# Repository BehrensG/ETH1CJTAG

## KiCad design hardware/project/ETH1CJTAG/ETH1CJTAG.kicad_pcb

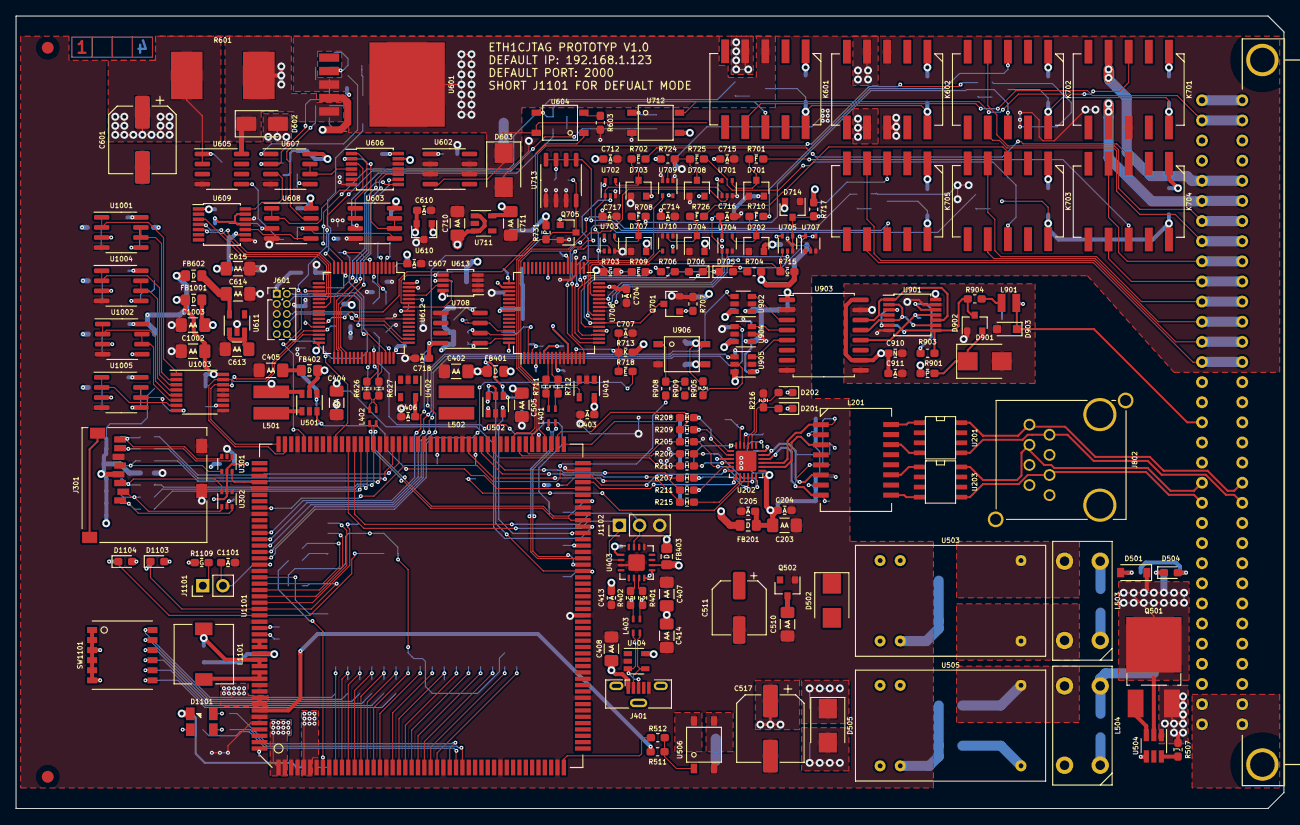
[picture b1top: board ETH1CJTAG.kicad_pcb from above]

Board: 4 copper layers, 160.0 x 100.0 mm, 458 parts (0 on the bottom side), 342 nets.

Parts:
C201, C202, C204, C205, C206, C207, C210, C212, C301, C302, C303, C403, C406, C409, C412, C413, C606, C607, C609, C612, C616, C619, C620, C621, C622, C626, C627, C628, C629, C630, C702, C704, C706, C707, C712, C713, C714, C715, C716, C717, C718, C719, C720, C721, C722, C723, C724, C901, C902, C903, C904, C905, C906, C907, C909, C911, C1001, C1005, C1006, C1007, C1008, C1009, C1101, C1104, C1105: 100n; C_0603_A_Pad1.05x0.95mm_HandSolder
C203, C304, C401, C402, C404, C405, C407, C408, C414, C502, C503, C505, C506, C509, C510, C613, C614, C615, C705, C710, C711, C725, C1002, C1003, C1103: 10u; C_1206_AA_Pad1.42x1.75mm_HandSolder
C208: 470p; C_0603_1608Metric_Pad1.05x0.95mm_HandSolder
C209, C605, C611, C908, C910, C1004: 1u; R_0603_N_Pad1.05x0.95mm_HandSolder
C211, C215: 1n/2kV; C_1206_3216Metric_Pad1.42x1.75mm_HandSolder
C213, C214, C624, C625, C708, C709: 8p; C_0603_S_Pad1.05x0.95mm_HandSolder
C410, C411, C912: 47p; C_0603_1608Metric_Pad1.05x0.95mm_HandSolder
C501, C504: 27p; C_0603_1608Metric_Pad1.05x0.95mm_HandSolder
C507, C512, C513, C518: 470p/2kV; C_1206_3216Metric_Pad1.42x1.75mm_HandSolder
C508, C514: 2u2/100V; C_1206_3216Metric_Pad1.42x1.75mm_HandSolder
C511: 100u; CP_Elec_6.3x5.9
C515, C516, C602, C603, C604: 10u/50V; C_1206_3216Metric_Pad1.42x1.75mm_HandSolder
C517, C601: 220u/50V; CP_Elec_8x6.9
C608, C623, C701, C703, C1102: 4u7; C_0805_M_Pad1.15x1.40mm_HandSolder
C610: 10u; C_0603_A_Pad1.05x0.95mm_HandSolder
C617, C618: 2u2; C_0603_1608Metric_Pad1.05x0.95mm_HandSolder
C631, C632: 2p2; C_0603_1608Metric_Pad1.05x0.95mm_HandSolder
D201: YELLLOW; LED_0603_1608Metric_Pad1.05x0.95mm_HandSolder
D202, D1103, D1104: GREEN; LED_0603_1608Metric_Pad1.05x0.95mm_HandSolder
D501: MMSZ5249B-E3-18; D_SOD-123
D502: P6SMB6.8CA; D_SMB
D503: SM6T30AY; DO_214AA_REV
D504: RED; LED_0603_1608Metric_Pad1.05x0.95mm_HandSolder
D505, D603: P6SMB30CA; D_SMB
D601, D604, D709, D710, D711, D712, D713: 1N4148W; D_SOD-123
D602: SK33A; D_SMA
D701, D702, D703, D704, D707, D708, D714: BAT54S; SOT-23
D705, D706: LED; LED_0603_1608Metric_Pad1.05x0.95mm_HandSolder
D901: SMBJ5.0A; D_SMB
D902: BAV99; SOT-23
D903: SD36C-01FTG; D_SOD-323_HandSoldering
D1101: 150121M153000
D1102: PMEG4005AEA; D_SOD-323
F501: MF-LSMF185/33X; Fuse_SMD2920
FB201, FB401, FB402, FB403, FB501, FB502, FB503, FB504, FB601, FB602, FB701, FB1001: 742792031; R_0805_D_Pad1.15x1.40mm_HandSolder
FID101, FID102, FID103, FID104: Fiducial; Fiducial_1.5mm_Mask3mm
J301: 693071010811
J401: 105133-0001; USB_Micro-B_Molex-105133-0001
J601: Conn_02x05; PinHeader_2x05_P1.27mm_Vertical
J801: C64AC; Socket_DIN41612-CaseC1-AC-Male-64Pin-2rows
J802: 615008145221
J1101: Conn_01x02; PinHeader_1x02_P2.54mm_Vertical
J1102: Conn_01x03_Male; PinHeader_1x03_P2.54mm_Vertical
J1103: Conn_02x10_Counter_Clockwise; PinHeader_2x10_P1.27mm_Vertical_SMD
K601, K602, K701, K702, K703, K704, K705: TQ2SA-5V; SA
L201: 749010012A
L401, L402, L403: 744233121
L501, L502: 4u7; 744031004
L503, L504: 7448014501
L901: CW252016-R33G; CW252016
L1101: 851-CDRH74NP-180MC; CDRH74
Q501: IRFR5410; TO-252-2_Rectifier
Q502: TSM2323; SOT-23
Q601, Q602: MMBT3904; SOT-23
Q603, Q702, Q703, Q704, Q705: BC847; SOT-23
Q701: 2SD1048; SOT-23
R201, R202, R203, R204, R1147: 49R9; R_0603_1608Metric_Pad1.05x0.95mm_HandSolder
R205, R206, R207, R208, R209, R210, R211, R215, R626, R627, R711, R712, R1110, R1111, R1112, R1113, R1114, R1115: 22; R_0603_H_Pad1.05x0.95mm_HandSolder
R212: 12k1; R_0603_1608Metric_Pad1.05x0.95mm_HandSolder
R213, R214: 75/1%; R_0603_1608Metric_Pad1.05x0.95mm_HandSolder
R216, R220, R221, R222, R301, R302, R303, R304, R305, R306, R503, R506, R612, R618, R619, R623, R703, R715, R716, R720, R721, R722, R905, R1003, R1004, R1007, R1008, R1011, R1012, R1015, R1016, R1109, R1117, R1118, R1119, R1120, R1121, R1122, R1123, R1124, R1125, R1128, R1129, R1130, R1131, R1132, R1133, R1134, R1135, R1144, R1146, R1148: 10k; R_0603_G_Pad1.05x0.95mm_HandSolder
R217, R218, R1142, R1143: 470; R_0603_1608Metric_Pad1.05x0.95mm_HandSolder
R219: 1M/1kV; R_1206_3216Metric_Pad1.42x1.75mm_HandSolder
R401, R402: 22; R_0603_G_Pad1.05x0.95mm_HandSolder
R501, R504: 180k; R_0603_1608Metric_Pad1.05x0.95mm_HandSolder
R502, R505: 20k; R_0603_1608Metric_Pad1.05x0.95mm_HandSolder
R507, R622, R630, R631, R1001: 100k; R_0603_J_Pad1.05x0.95mm_HandSolder
R508: 6k8/0.5W; R_0805_2012Metric_Pad1.15x1.40mm_HandSolder
R509: 370; R_0603_1608Metric_Pad1.05x0.95mm_HandSolder
R510, R907: 0/0.75W; R_1206_3216Metric_Pad1.42x1.75mm_HandSolder
R511, R512, R603, R727, R908, R909: 420; R_0603_1608Metric_Pad1.05x0.95mm_HandSolder
R601: WSR21R000FEB; WSR
R602, R610: 100/0.1%; R_0603_1608Metric_Pad1.05x0.95mm_HandSolder
R604, R605: 50k/0.1%; R_0603_1608Metric_Pad1.05x0.95mm_HandSolder
R606, R607: 22k/0.1%; R_0603_1608Metric_Pad1.05x0.95mm_HandSolder
R608, R1106, R1107: 330; R_0603_1608Metric_Pad1.05x0.95mm_HandSolder
R609: 1k/0.1%; R_0603_1608Metric_Pad1.05x0.95mm_HandSolder
R611, R709, R718, R730, R1101, R1102, R1103, R1104, R1145: 0; R_0603_E_Pad1.05x0.95mm_HandSolder
R613, R615, R616, R617: 10k/0.1%; R_0603_1608Metric_Pad1.05x0.95mm_HandSolder
R614: 3k2; R_0603_L_Pad1.05x0.95mm_HandSolder
R620, R628, R629, R632, R633, R713: 4k7; R_0603_K_Pad1.05x0.95mm_HandSolder
R621, R728, R729, R731, R732, R733, R901: 1k; R_0603_P_Pad1.05x0.95mm_HandSolder
R624, R625: 560; R_0603_1608Metric_Pad1.05x0.95mm_HandSolder
R701, R702, R708, R710, R719, R725, R726: 82; R_0603_F_Pad1.05x0.95mm_HandSolder
R704, R706: 270; R_0603_1608Metric_Pad1.05x0.95mm_HandSolder
R705: 15k; R_0603_1608Metric_Pad1.05x0.95mm_HandSolder
R707, R717, R724: 22k; R_0603_1608Metric_Pad1.05x0.95mm_HandSolder
R714: 12k; R_0603_1608Metric_Pad1.05x0.95mm_HandSolder
R723: 2k2; R_0603_1608Metric_Pad1.05x0.95mm_HandSolder
R902: 14k7; R_0603_1608Metric_Pad1.05x0.95mm_HandSolder
R903: 100; R_0603_1608Metric_Pad1.05x0.95mm_HandSolder
R904: 47; R_0603_1608Metric_Pad1.05x0.95mm_HandSolder
R906: 51R1; R_0603_1608Metric_Pad1.05x0.95mm_HandSolder
R1002, R1006, R1014: 5k; R_0603_1608Metric_Pad1.05x0.95mm_HandSolder
R1005, R1009, R1010, R1013: 13k; R_0603_1608Metric_Pad1.05x0.95mm_HandSolder
R1105: 523; R_0603_1608Metric_Pad1.05x0.95mm_HandSolder
R1108: 1k5; R_0603_1608Metric_Pad1.05x0.95mm_HandSolder
R1116: 75k; R_0603_1608Metric_Pad1.05x0.95mm_HandSolder
R1126: 130k; R_0603_1608Metric_Pad1.05x0.95mm_HandSolder
R1127: 680k; R_0603_1608Metric_Pad1.05x0.95mm_HandSolder
R1136, R1137, R1138, R1139, R1140, R1141: 47k; R_0603_I_Pad1.05x0.95mm_HandSolder
SW1101: TDA06H0B1
U201, U203: LC03-3.3; SO8E
U202: LAN8720A; QFN-24-1EP_4x4mm_P0.5mm_EP2.6x2.6mm
U204, U301, U302: 82400274; SOT-363_SC-70-6
U401, U402, U404: 824011; SOT-23-5
U403: FT230XQ; QFN-16-1EP_4x4mm_P0.65mm_EP2.1x2.1mm
U501, U502: TPS61073; SOT-23-6
U503: TEL 10-2411WI; TEL10
U504: MAX5902; SOT-23-6_Handsoldering
U505: TEL 10-2415WI; TEL10
U506, U604, U712, U906: AQY212GS
U601: LT3080EQ; DD-PAK
U602: LM334M; SOIC-8_3.9x4.9mm_P1.27mm
U603, U607, U608, U1001, U1002, U1004, U1005: TLC272; SOIC-8_3.9x4.9mm_P1.27mm
U605: MAX4080FASA+; SOIC-8_3.9x4.9mm_P1.27mm
U606: MCP3204; TSSOP-14_4.4x5mm_P0.65mm
U609: MCP4922-ESL; TSSOP-14_4.4x5mm_P0.65mm
U610: REF3025; SOT-23
U611, U711: TLV75533PDBV; SOT-23-5
U612: STM32F405RGT6; LQFP-64_10x10mm_P0.5mm
U613: 24LC256; MSOP-8_3x3mm_P0.65mm
U701, U702, U703, U704, U705, U707, U709, U710: NC7SZ125; SOT-353_SC-70-5
U706: FT2232H; LQFP-64_10x10mm_P0.5mm
U708: 93LC56; SOIC-8_3.9x4.9mm_P1.27mm
U713: IRF7455; SO-8_3.9x4.9mm_P1.27mm
U901: 74AC125; TSSOP-14_4.4x5mm_P0.65mm
U902, U904, U905: SN74LVC1T45DBV; SOT-23-6
U903: ADuM5402; SOIC-16W_7.5x10.3mm_P1.27mm
U1003: ADS7828; TSSOP-16_4.4x5mm_P0.65mm
U1101: chiliSOM; GCS2
Y201: ECS-250-8-36CKM-TR; ECX-2236
Y601, Y701: ECS-120-8-36-CKM-TR; ECX-2236
Y602: 32.768kHz; ABS06W

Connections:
3.3V_DBG: C412.1, U403.1, U403.8, U403.9
5V_ISO_TRIG: C909.1, C910.1, C911.1, R901.1, U901.14, U903.10, U903.16
5V_TRIG: C904.1, C905.1, C906.1, C907.1, C908.1, R905.2, R907.2, U902.1, U903.1, U904.1, U905.1, U906.4
5V_USB: C407.1, C413.1, C414.1, FB403.2, U403.10, U1101.5, U1101.6
+1.8V_JTAG: C705.1, C706.1, U706.12, U706.37, U706.49, U706.64
+2V5: C610.1, R611.2, U606.13, U609.11, U609.13, U610.2
+3.3VA: R511.2, R909.2, U1101.178
+3.3V_D: C201.1, C202.1, C301.1, C302.1, C303.1, C304.1, C901.1, C902.1, C903.1, C1003.1, C1104.1, D1101.1, FB201.2, FB1001.1, J301.4, J1103.3, R220.1, R221.1, R222.1, R301.1, R302.1, R303.1, R304.1, R305.1, R306.1, R1014.1, R1108.1, R1109.1, R1117.1, R1118.1, R1119.1, R1142.1, R1143.1, R1144.1, R1146.1, R1148.1, SW1101.1, SW1101.2, SW1101.3, SW1101.4, SW1101.5, SW1101.6, U202.9, U301.5, U302.5, U902.6, U904.6, U905.6, U1101.176, U1101.177
+3.3V_JTAG: C701.1, C702.1, C703.1, C704.1, C712.1, C713.1, C714.1, C715.1, C716.1, C717.1, C718.1, C719.1, C720.1, C721.1, C722.1, C723.1, C724.1, C725.1, D701.2, D702.2, D703.2, D704.2, D707.2, D708.2, D714.2, FB701.1, R703.1, R704.1, R705.2, R706.1, R713.1, R715.2, R716.2, R717.1, R720.1, R721.1, R722.1, R724.1, R731.2, R1002.1, U701.5, U702.5, U703.5, U704.5, U705.5, U706.4, U706.9, U706.20, U706.31, U706.42, U706.50, U706.56, U707.5, U708.8, U709.5, U710.5, U712.3
+3.3V_PSU: C611.1, C612.1, C615.1, C619.1, C620.1, C621.1, C622.1, C623.1, C626.1, C627.1, C628.1, FB601.1, FB602.1, J601.1, R614.1, R620.1, R622.1, R628.1, R629.1, R632.1, R633.1, R1006.1, U603.8, U606.14, U607.8, U609.1, U609.9, U610.1, U612.19, U612.32, U612.48, U612.64, U613.8
+3.3V_TEST: C1002.1, C1004.1, C1005.1, C1006.1, C1007.1, C1008.1, C1009.1, FB1001.2, U1001.8, U1002.8, U1003.16, U1004.8, U1005.8
+5VD: C511.1, D601.1, D604.1, D709.1, D710.1, D711.1, D712.1, D713.1, K601.1, K602.1, K701.1, K702.1, K703.1, K704.1, K705.1, Q502.2, R907.1, R1005.1, U906.3, U1101.1, U1101.2
+24V: F501.1, J801.A31, J801.A32, J801.C31, J801.C32
+24V_PSU: C601.1, C629.1, C630.1, R510.1, R601.2, R1001.1, U506.4, U601.4, U605.1, U605.2, U608.8
/Connector/+VOUT: J801.A1, J801.C1, K601.4
/Connector/-VOUT: J801.A3, J801.C3, K602.4, K602.7
/Connector/EXT_TRIG: C912.1, D903.1, J801.A17, L901.1
/Connector/JTAG_GND: J801.A6, J801.C6, K701.7
/Connector/JTAG_VCC: J801.A5, J801.C5, K701.4
/Connector/RCTK: J801.A11, J801.C11, K703.4
/Connector/RX+: J801.A20, J802.3, U203.8
/Connector/RX-: J801.A21, J802.6, U203.5
/Connector/SENSE: J801.A2, J801.C2, K601.7
/Connector/SRST: J801.A13, J801.C13, K705.4
/Connector/TCK: J801.A10, J801.C10, K704.7
/Connector/TDI: J801.A8, J801.C8, K702.7
/Connector/TDO: J801.A12, J801.C12, K703.7
/Connector/TMS: J801.A9, J801.C9, K704.4
/Connector/TRST: J801.A7, J801.C7, K702.4
/Connector/TX+: J801.C20, J802.1, U201.8
/Connector/TX-: J801.C21, J802.2, U201.5
/Connector/nRESET: J801.A14, J801.C14, K705.7
/Ethernet/ETH_CRS_DV: R211.2, U1101.106
/Ethernet/ETH_MDC: U202.13, U1101.89
/Ethernet/ETH_MDIO: R1108.2, U202.12, U1101.90
/Ethernet/ETH_MODE0: R208.1, R220.2, U202.8
/Ethernet/ETH_MODE1: R209.1, R221.2, U202.7
/Ethernet/ETH_MODE2: R211.1, R222.2, U202.11
/Ethernet/ETH_RD_N: L201.8, R204.2, U202.22, U204.1
/Ethernet/ETH_RD_P: L201.6, R203.2, U202.23, U204.3
/Ethernet/ETH_REFCLK: R215.2, U1101.108
/Ethernet/ETH_RESETn: C212.1, R1104.1, U202.15
/Ethernet/ETH_RXD0: R208.2, U1101.93
/Ethernet/ETH_RXD1: R209.2, U1101.94
/Ethernet/ETH_RXERR: R210.2, U1101.104
/Ethernet/ETH_TD_N: L201.3, R202.2, U202.20, U204.4
/Ethernet/ETH_TD_P: L201.1, R201.2, U202.21, U204.6
/Ethernet/ETH_TXD0: R205.2, U1101.99
/Ethernet/ETH_TXD1: R206.2, U1101.100
/Ethernet/ETH_TXEN: R207.2, U1101.105
/JTAG/3V3_JTAG_CTR: R727.2, U1101.134
/JTAG/FT_EECLK: R721.2, U706.62, U708.2
/JTAG/FT_EECS: R720.2, U706.63, U708.1
/JTAG/FT_EEDATA: R723.1, U706.61, U708.3
/JTAG/FT_JTAG_OE_N: R703.2, R709.1, U701.1, U702.1, U703.1
/JTAG/FT_RCTK: U706.24, U710.4
/JTAG/FT_SRST_N_IN: D706.1, U706.23, U707.4
/JTAG/FT_SRST_N_OE_N: R715.1, U705.1, U706.29
/JTAG/FT_SRST_N_OUT: U705.2, U706.27
/JTAG/FT_TCK_OUT: U701.2, U706.16
/JTAG/FT_TDI_OUT: U703.2, U706.17
/JTAG/FT_TDO_IN: U706.18, U709.4
/JTAG/FT_TMS_OUT: U702.2, U706.19
/JTAG/FT_TRST_N_OE_N: R716.1, U704.1, U706.28
/JTAG/FT_TRST_N_OUT: U704.2, U706.26
/JTAG/FT_VREF_N_IN: D705.1, Q701.3, U706.22
/JTAG/FT_~RESET: R718.2, U1101.154
/JTAG/F_USB1_D_N: L401.3, R712.2, U401.4
/JTAG/F_USB1_D_P: L401.2, R711.2, U401.3
/JTAG/JTAG_REL1: D711.2, D712.2, K703.10, K704.10, Q704.3
/JTAG/JTAG_REL2: D709.2, D710.2, K701.10, K702.10, Q702.3
/JTAG/JTAG_REL3: D713.2, K705.10, Q703.3
/JTAG/JTAG_REL_CTR1: R732.2, U1101.96
/JTAG/JTAG_REL_CTR2: R728.2, U1101.101
/JTAG/JTAG_REL_CTR3: R729.2, U1101.98
/JTAG/RCTK1: K703.3, R726.1
/JTAG/RCTK1_A: D704.3, R726.2, U710.2
/JTAG/SRST1: K705.3, R719.1
/JTAG/SRST1_A: D714.3, R717.2, R719.2, U705.4, U707.2
/JTAG/TCK1: K704.8, R701.1
/JTAG/TCK1_A: D701.3, R701.2, U701.4
/JTAG/TDI1: K702.8, R708.1
/JTAG/TDI1_A: D707.3, R708.2, U703.4
/JTAG/TDO1: K703.8, R725.1
/JTAG/TDO1_A: D708.3, R724.2, R725.2, U709.2
/JTAG/TMS1: K704.3, R702.1
/JTAG/TMS1_A: D703.3, R702.2, U702.4
/JTAG/TRST1: K702.3, R710.1
/JTAG/TRST1_A: D702.3, R710.2, U704.4
/JTAG/nRESET1: K705.8, R730.1, U713.5, U713.6, U713.7, U713.8
/JTAG/nRESET_OUT: R733.2, U1101.150
/PSU/CLIM: Q602.3, U612.16
/PSU/F_USB0_D_N: L402.2, R626.1, U402.4
/PSU/F_USB0_D_P: L402.3, R627.1, U402.3
/PSU/I2C_SCL: R632.2, U612.29, U1003.14, U1101.138
/PSU/I2C_SDA: R633.2, U612.30, U1003.15, U1101.137
/PSU/ISET: U608.5, U609.10
/PSU/NC\TDI: J601.8, U612.50
/PSU/PSU_ADC_CLK: U606.11, U612.34
/PSU/PSU_ADC_IOUT: C605.1, R608.1, U603.5, U608.6
/PSU/PSU_ADC_SDI: U606.9, U612.36
/PSU/PSU_ADC_SDO: U606.10, U612.35
/PSU/PSU_ADC_VOUT: C606.1, R604.1, R606.2, R607.2, U603.3
/PSU/PSU_ADC_~CS: U606.8, U612.33
/PSU/PSU_DAC_SCK: U609.4, U612.21
/PSU/PSU_DAC_SDI: U609.5, U612.23
/PSU/PSU_DAC_~CS: U609.3, U612.20
/PSU/PSU_I2C_SCL: R628.2, U612.58, U613.6
/PSU/PSU_I2C_SDA: R629.2, U612.59, U613.5
/PSU/PSU_NRST: C616.1, J601.10, R620.2, U612.7, U1101.129
/PSU/PSU_RELAY: D601.2, D604.2, K601.10, K602.10, Q603.3
/PSU/PSU_SENSE: U604.1, U612.27
/PSU/PSU_WP: U612.61, U613.7
/PSU/SWDCLK\TCK: J601.4, U612.49
/PSU/SWDIO\TMS: J601.2, U612.46
/PSU/SWO\TDO: J601.6, U612.55
/PSU/USB0_ID: R625.1, R1101.2, R1102.1
/PSU/VSET: U607.3, U609.14
/Power/ENA_24V_PSU: R512.2, U1101.46
/Power/USB0_DRVVBUS: R503.1, U501.3, U1101.88
/Power/USB1_DRVVBUS: R506.1, U502.3, U1101.81
/SOM/BOOT0: R1125.2, R1141.1, U1101.10
/SOM/BOOT1: R1124.2, R1140.1, U1101.11
/SOM/BOOT2: R1123.2, R1139.1, U1101.12
/SOM/BOOT3: R1122.2, R1138.1, U1101.13
/SOM/BOOT4: R1121.2, R1137.1, U1101.14
/SOM/BOOT5: R1120.2, R1136.1, U1101.15
/SOM/BOOT6: R1119.2, U1101.16
/SOM/BOOT7: R1135.1, U1101.17
/SOM/BOOT8: R1134.1, U1101.19
/SOM/BOOT9: R1118.2, R1133.1, U1101.20
/SOM/BOOT10: R1132.1, U1101.21
/SOM/BOOT11: R1131.1, U1101.22
/SOM/BOOT12: R1130.1, U1101.23
/SOM/BOOT13: R1129.1, U1101.24
/SOM/BOOT14: R1117.2, U1101.25
/SOM/BOOT15: R1128.1, U1101.26
/SOM/DBG_RXD: J1102.2, U403.15, U1101.126
/SOM/DBG_TXD: J1102.1, U403.2, U1101.127
/SOM/ENA_5V_TRIG: R908.2, U1101.146
/SOM/LED_BLUE: R1107.2, U1101.28
/SOM/LED_GREEN: R1106.2, U1101.30
/SOM/LED_RED: R1105.2, U1101.29
/SOM/SD_CD: J301.9, R306.2, U301.6, U1101.142
/SOM/SD_CLK: J301.5, R1110.2, U301.4
/SOM/SD_CMD: J301.3, R303.2, R1111.2, U302.6
/SOM/SD_DAT0: J301.7, R304.2, R1112.2, U301.1
/SOM/SD_DAT1: J301.8, R305.2, R1113.2, U301.3
/SOM/SD_DAT2: J301.1, R301.2, R1114.2, U302.3
/SOM/SD_DAT3: J301.2, R302.2, R1115.2, U302.1
/SOM/TRIG_EN: U902.4, U1101.153
/SOM/TRIG_IN: U905.4, U1101.151
/SOM/TRIG_OUT: U904.4, U1101.152
/SOM/USB0_D_N: L402.1, U1101.83
/SOM/USB0_D_P: L402.4, U1101.84
/SOM/USB1_D_N: L401.4, U1101.76
/SOM/USB1_D_P: L401.1, U1101.77
/SOM/chili_EMU0: D1104.1, J1103.7, R1144.2, U1101.163
/SOM/chili_EMU1: D1103.1, J1103.14, R1146.2, U1101.162
/SOM/chili_RESETn: C1105.1, R1147.2, R1148.2, U1101.8
/SOM/chili_TCK: J1103.6, R1145.2, U1101.158
/SOM/chili_TDI: J1103.2, U1101.160
/SOM/chili_TDO: J1103.4, U1101.159
/SOM/chili_TMS: J1103.1, U1101.161
/SOM/chili_~TRST: J1103.20, U1101.157
/Test/CH0: U1001.1, U1001.2, U1003.1
/Test/CH1: U1001.6, U1001.7, U1003.2
/Test/CH2: U1003.3, U1004.1, U1004.2
/Test/CH3: U1003.4, U1004.6, U1004.7
/Test/CH4: U1002.1, U1002.2, U1003.5
/Test/CH5: U1002.6, U1002.7, U1003.6
/Test/CH6: U1003.7, U1005.1, U1005.2
/Test/CH7: U1003.8, U1005.6, U1005.7
/Trigger/EXT_TRIG_SIGN: R902.1, U901.11, U903.12
/Trigger/TRIG_OUT_EN: U901.1, U901.4, U901.10, U903.14
/Trigger/TRIG_OUT_SIGN: U901.2, U901.5, U901.9, U903.13
/USB/DBG_USB_D_N: C410.1, L403.1, R401.1
/USB/DBG_USB_D_P: C411.1, L403.4, R402.1
/USB/F_DBG_USB_D_N: J401.2, L403.2, U404.4
/USB/F_DBG_USB_D_P: J401.3, L403.3, U404.3
DBG_USB_VCC: C408.1, C409.1, FB403.1, J401.1, U404.5
Earth: C211.2, C215.1, J801.A19, J801.A23, J801.C19, J801.C23, J802.SH, R219.1
GND: C909.2, C910.2, C911.2, D901.2, D902.1, D903.2, J801.C17, R906.2, U901.7, U901.13, U903.9, U903.15
GNDA: C201.2, C202.2, C203.2, C204.2, C205.2, C206.2, C207.2, C208.2, C209.2, C210.2, C212.2, C213.2, C214.2, C215.2, C301.2, C302.2, C303.2, C304.2, C401.2, C402.2, C403.2, C404.2, C405.2, C406.2, C407.2, C408.2, C409.2, C410.2, C411.2, C412.2, C413.2, C414.2, C502.2, C503.2, C505.2, C506.2, C510.2, C511.2, C516.2, C517.2, C601.2, C602.2, C603.2, C604.2, C605.2, C606.2, C607.2, C608.2, C609.2, C610.2, C611.2, C612.2, C613.2, C614.2, C615.2, C616.2, C617.2, C618.2, C619.2, C620.2, C621.2, C622.2, C623.2, C624.2, C625.2, C626.2, C627.2, C628.2, C629.2, C630.2, C631.2, C632.2, C701.2, C702.2, C703.2, C704.2, C705.2, C706.2, C707.2, C708.2, C709.2, C710.2, C711.2, C712.2, C713.2, C714.2, C715.2, C716.2, C717.2, C718.2, C719.2, C720.2, C721.2, C722.2, C723.2, C724.2, C725.2, C901.2, C902.2, C903.2, C904.2, C905.2, C906.2, C907.2, C908.2, C1001.2, C1002.2, C1003.2, C1004.2, C1005.2, C1006.2, C1007.2, C1008.2, C1009.2, C1101.2, C1102.1, C1103.2, C1104.2, C1105.2, D603.2, D701.1, D702.1, D703.1, D704.1, D707.1, D708.1, D714.1, FB502.2, FB504.2, J301.6, J301.10, J401.5, J601.3, J601.5, J1102.3, J1103.11, J1103.13, J1103.15, J1103.16, J1103.17, J1103.19, K602.3, K602.8, K701.8, Q502.1, Q601.2, Q602.2, Q603.2, Q701.2, Q702.2, Q703.2, Q704.2, Q705.2, R212.1, R216.2, R217.2, R218.2, R219.2, R502.2, R503.2, R505.2, R506.2, R602.2, R603.1, R606.1, R607.1, R613.2, R615.2, R618.2, R623.2, R630.1, R631.1, R707.1, R714.2, R1003.2, R1004.2, R1007.2, R1008.2, R1011.2, R1012.2, R1015.2, R1016.2, R1101.1, R1103.1, R1116.2, R1126.1, R1127.1, R1128.2, R1129.2, R1130.2, R1131.2, R1132.2, R1133.2, R1134.2, R1135.2, R1136.2, R1137.2, R1138.2, R1139.2, R1140.2, R1141.2, U202.25, U204.2, U301.2, U302.2, U401.2, U402.2, U403.3, U403.13, U403.17, U404.2, U501.2, U502.2, U506.2, U602.2, U602.3, U602.6, U602.7, U603.4, U605.4, U606.7, U606.12, U607.4, U608.4, U609.8, U609.12, U610.3, U611.2, U612.12, U612.18, U612.63, U613.1, U613.2, U613.3, U613.4, U701.3, U702.3, U703.3, U704.3, U705.3, U706.1, U706.5, U706.10, U706.11, U706.13, U706.15, U706.25, U706.35, U706.47, U706.51, U707.1, U707.3, U708.5, U709.1, U709.3, U710.1, U710.3, U711.2, U712.2, U713.1, U713.2, U713.3, U902.2, U902.5, U903.2, U903.8, U904.2, U904.5, U905.2, U906.2, U1001.4, U1002.4, U1003.9, U1003.11, U1003.12, U1003.13, U1004.4, U1005.4, U1101.3, U1101.4, U1101.9, U1101.18, U1101.27, U1101.36, U1101.45, U1101.55, U1101.68, U1101.78, U1101.85, U1101.91, U1101.97, U1101.109, U1101.118, U1101.121, U1101.130, U1101.135, U1101.143, U1101.147, U1101.156, U1101.164, U1101.174, U1101.175, U1101.179, U1101.180, Y201.2, Y201.4, Y601.2, Y601.4, Y701.2, Y701.4
GNDPWR: C508.2, C514.2, D503.2, D504.1, J801.A27, J801.A28, J801.C27, J801.C28, L503.2, L504.2, U504.4
unnamed: C203.1, C204.1, C205.1, C206.1, C207.1, C210.1, FB201.1, L201.2, L201.7, R201.1, R202.1, R203.1, R204.1, U202.1, U202.19
unnamed: C208.1, C209.1, U202.6
unnamed: C211.1, R213.2, R214.2
unnamed: C213.1, U202.5, Y201.1
unnamed: C214.1, U202.4, Y201.3
unnamed: C501.2, R501.2, R502.1, U501.4
unnamed: C504.2, R504.2, R505.1, U502.4
unnamed: C507.1, L503.4, U503.16
unnamed: C507.2, C509.2, C512.2, D502.2, FB502.1, U503.10
unnamed: C508.1, C514.1, D501.1, L503.1, L504.1, Q501.2, R508.1, U504.2
unnamed: C509.1, D502.1, FB501.1, U503.9
unnamed: C510.1, FB501.2, Q502.3
unnamed: C512.1, L503.3, U503.1
unnamed: C513.1, L504.4, U505.16
unnamed: C513.2, C515.2, C518.2, D505.2, FB504.1, U505.10
unnamed: C515.1, D505.1, FB503.1, U505.9
unnamed: C516.1, C517.1, FB503.2, R510.2, U506.3
unnamed: C518.1, L504.3, U505.1
unnamed: C602.1, D602.2, D603.1, K601.3, U601.3, U601.6, U602.4, U604.4
unnamed: C603.1, D602.1, R601.1, U601.5, U605.8
unnamed: C604.1, R610.1, R617.1, U601.2
unnamed: C607.1, U612.1
unnamed: C608.1, C609.1, FB601.2, U612.13
unnamed: C614.1, FB602.2, U611.5
unnamed: C617.1, U612.31
unnamed: C618.1, U612.47
unnamed: C624.1, U612.5, Y601.3
unnamed: C625.1, U612.6, Y601.1
unnamed: C631.1, U612.4, Y602.1
unnamed: C632.1, U612.3, Y602.2
unnamed: C707.1, R713.2, R718.1, U706.14
unnamed: C708.1, U706.2, Y701.1
unnamed: C709.1, U706.3, Y701.3
unnamed: C711.1, FB701.2, U711.5
unnamed: C912.2, R906.1
unnamed: C1001.1, U1003.10
unnamed: C1101.1, J1101.2, U1101.155
unnamed: C1102.2, D1102.1, U1101.169
unnamed: C1103.1, U1101.113
unnamed: D201.1, R217.1
unnamed: D201.2, R216.1, U202.2
unnamed: D202.1, R218.1
unnamed: D202.2, U202.3
unnamed: D501.2, R509.1
unnamed: D503.1, F501.2, Q501.3, R507.1, U504.1
unnamed: D504.2, R508.2, R509.2
unnamed: D705.2, R704.2
unnamed: D706.2, R706.2
unnamed: D901.1, D902.2, R901.2
unnamed: D902.3, R903.2, R904.1, U901.3, U901.6, U901.8
unnamed: D1101.2, R1105.1
unnamed: D1101.3, R1106.1
unnamed: D1101.4, R1107.1
unnamed: D1102.2, L1101.2, U1101.170, U1101.171
unnamed: D1103.2, R1142.2
unnamed: D1104.2, R1143.2
unnamed: J1101.1, R1109.2
unnamed: J1103.5, R1145.1
unnamed: J1103.8, R1147.1
unnamed: K601.8, R605.2, U604.3
unnamed: K701.3, U712.4
unnamed: L201.9, U203.4
unnamed: L201.10, R213.1
unnamed: L201.11, U203.1
unnamed: L201.14, U201.4
unnamed: L201.15, R214.1
unnamed: L201.16, U201.1
unnamed: L501.2, U501.1
unnamed: L502.2, U502.1
unnamed: L901.2, R904.2
unnamed: Q501.1, U504.3
unnamed: Q601.1, R612.1
unnamed: Q601.3, R609.1, R610.2
unnamed: Q602.1, R619.1
unnamed: Q603.1, R621.1
unnamed: Q701.1, R705.1, R707.2
unnamed: Q702.1, R728.1
unnamed: Q703.1, R729.1
unnamed: Q704.1, R732.1
unnamed: Q705.1, R733.1
unnamed: Q705.3, R730.2, R731.1, U713.4
unnamed: R205.1, U202.17
unnamed: R206.1, U202.18
unnamed: R207.1, U202.16
unnamed: R210.1, U202.10
unnamed: R212.2, U202.24
unnamed: R215.1, U202.14
unnamed: R401.2, U403.7
unnamed: R402.2, U403.6
unnamed: R507.2, U504.6
unnamed: R511.1, R512.1, U506.1
unnamed: R602.1, U602.1
unnamed: R603.2, U604.2
unnamed: R604.2, R605.1
unnamed: R608.2, U605.5
unnamed: R609.2, U607.1
unnamed: R611.1, U608.3
unnamed: R612.2, R619.2, U608.7
unnamed: R613.1, R615.1, R616.2, U607.2
unnamed: R614.2, R618.1, U607.5
unnamed: R616.1, R617.2
unnamed: R621.2, U612.14
unnamed: R622.2, R625.2, U612.43
unnamed: R623.1, U612.60
unnamed: R624.2, U612.42
unnamed: R626.2, U612.44
unnamed: R627.2, U612.45
unnamed: R630.2, U612.28
unnamed: R631.2, U612.57
unnamed: R709.2, U706.21
unnamed: R711.1, U706.7
unnamed: R712.1, U706.8
unnamed: R714.1, U706.6
unnamed: R722.2, R723.2, U708.4
unnamed: R727.1, U712.1
unnamed: R902.2, R903.1, U901.12
unnamed: R905.1, U905.5
unnamed: R908.1, R909.1, U906.1
unnamed: R1001.2, R1003.1, U1001.3
unnamed: R1002.2, R1004.1, U1002.3
unnamed: R1005.2, R1007.1, U1001.5
unnamed: R1006.2, R1008.1, U1002.5
unnamed: R1009.2, R1011.1, U1004.3
unnamed: R1010.2, R1012.1, U1005.3
unnamed: R1013.2, R1015.1, U1004.5
unnamed: R1014.2, R1016.1, U1005.5
unnamed: R1102.2, U1101.86
unnamed: R1103.2, U1101.79
unnamed: R1104.2, U1101.107
unnamed: R1110.1, U1101.122
unnamed: R1111.1, U1101.123
unnamed: R1112.1, U1101.120
unnamed: R1113.1, U1101.119
unnamed: R1114.1, U1101.125
unnamed: R1115.1, U1101.124
unnamed: R1116.1, U1101.184
unnamed: R1120.1, SW1101.7
unnamed: R1121.1, SW1101.8
unnamed: R1122.1, SW1101.9
unnamed: R1123.1, SW1101.10
unnamed: R1124.1, SW1101.11
unnamed: R1125.1, SW1101.12
unnamed: R1126.2, U1101.166
unnamed: R1127.2, U1101.165
unnamed: U603.1, U603.2, U606.1
unnamed: U603.6, U603.7, U606.2
unnamed: U606.3, U608.1, U608.2
unnamed: U606.4, U607.6, U607.7
unnamed: U902.3, U903.3
unnamed: U903.4, U904.3
unnamed: U903.5, U905.3
unnamed: U1101.167, U1101.168
USB0_VBUS: C404.1, C501.1, C502.1, FB402.2, R501.1, U501.5, U1101.82
USB0_VCC: C405.1, C406.1, C613.1, FB402.1, R624.1, R1009.1, U402.5, U611.1, U611.3
USB1_VBUS: C401.1, C504.1, C505.1, FB401.2, R504.1, U502.5, U1101.75
USB1_VCC: C402.1, C403.1, C710.1, FB401.1, R1013.1, U401.5, U711.1, U711.3
V_SYS: C503.1, C506.1, L501.1, L502.1, L1101.1, R1010.1, U501.6, U502.6, U1101.172, U1101.173

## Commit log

2019-06-16 Added hardware project folder structure
2019-06-16 Schematic library development. Added chiliSOM, ethernet, microUSB and USB schematics.
2019-06-16 Small changes
2019-06-17 Power supply schematic.
2019-06-20 PSU and Power schematic development
2019-06-21 Development
2019-07-03 Added Trigger.sch
2019-07-03 Added Test.sch
2019-07-07 Footprints
2019-07-09 Schematic update and check
2019-07-11 PCB layout
2019-07-12 PCB design
2019-07-27 PCB done
2019-07-28 PCB zones modified
2019-08-09 BOM created, footprint fixes.
2019-08-09 Modification of power planes
2019-08-12 Added pre-regulator circuit to the PSU. Need to redesing the PCB.
2019-08-13 PCB layout for the pre-regulator circuit. Missing EPOT.
2019-08-18 Footprints update
2019-08-26 Added new parts to BOM list. PCB ready.
2019-09-12 Changed capacitor 220u/50V to 100u/50V. 220u was too large for the DC/DC converter as capacitive load.
